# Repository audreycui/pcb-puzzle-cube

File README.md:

# pcb-puzzle-cube
Mechanical, Optical, &amp; Electronic Puzzle Cube

I made a puzzle cube for my wonderful electronics lab instructor who is also a professional trumpet player! A lot of the fun in making this was designing my circuits and mechanical components around 5 milled PCBs soldered together into a cube. Puzzles involve "playing" a sequence of notes on a flex PCB capacitive trumpet and using a butterfly flexure to align a laser path through a beamsplitter.

## Milled PCBs
From left to right, the sides of the cube include: 
1. WS2812b LEDs 
2. resistor combinations with pads for probing
3. laser diode regulated by a LM317 circuit and switched on/off electronically with a 2N7002 MOSFET 
4. QTPy ESP32 microcontroller
   
Sides 1 & 4 also include a photoresistor to detect laser beam alignment.

And the bottom:

5. 5V power jack, switches for the board power and laser power, mount for butterfly flexure

## Trumpet Capacitive Touch FlexPCB
I really wanted an excuse to fab a flexPCB, so I did so here. FlexPCB files are located in the <code>trumpet</code> subfolder. 

The connector end of the trumpet was designed to fit in a 6pin/1mm FPC connector. I ended up just soldering it directly to the board though, since I ended up finding an end mill small enough to carve out the 1mm pitch pads. It also helped me avoid buying an extra component. 

## Video Demo
Watch a video demo of the cube being solved [here](https://www.youtube.com/watch?v=AHTcb9tr4TA) :D

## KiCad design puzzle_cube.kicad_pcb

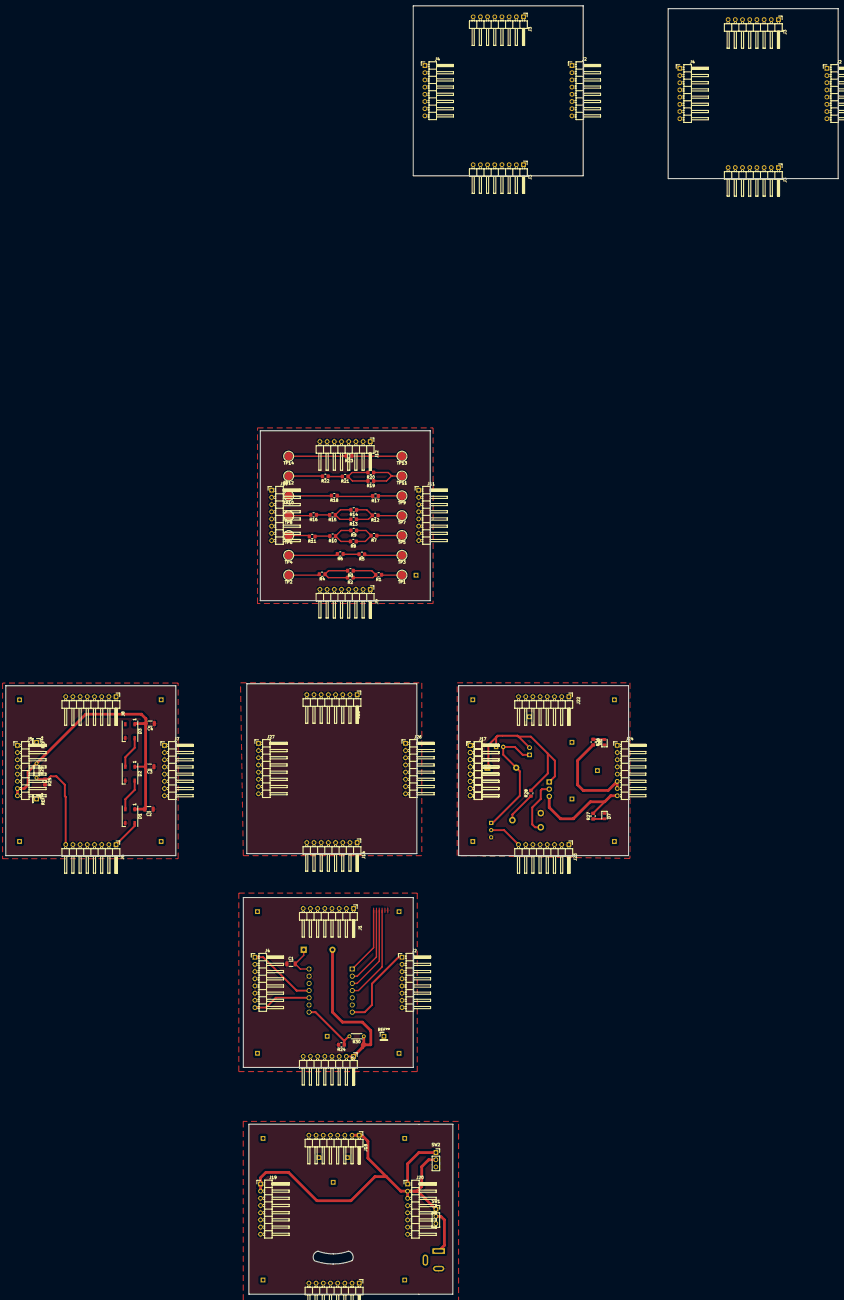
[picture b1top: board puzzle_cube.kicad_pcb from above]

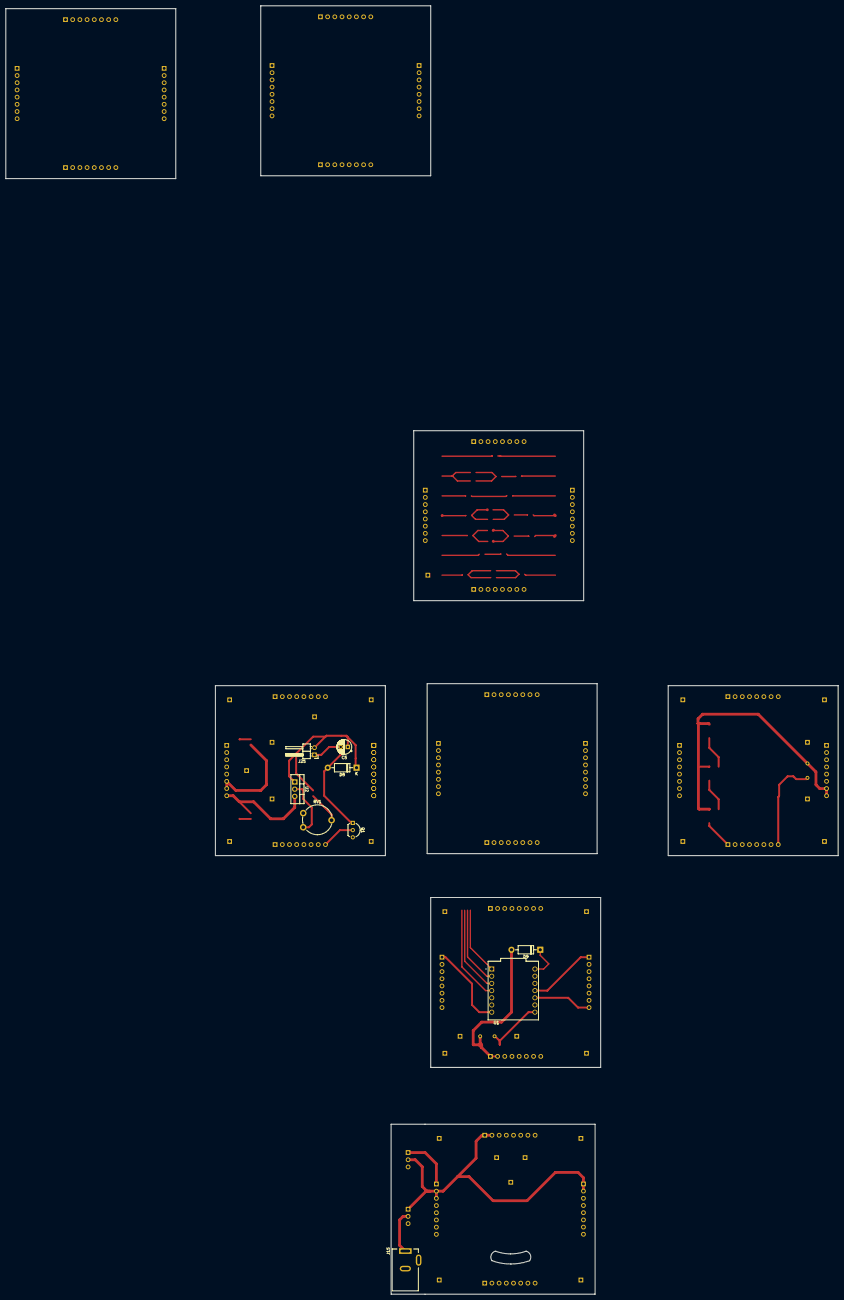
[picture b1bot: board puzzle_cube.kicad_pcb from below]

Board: 2 copper layers, 293.8 x 454.8 mm, 98 parts (9 on the bottom side), 47 nets.

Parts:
C1: C; C_1206_3216Metric
C2, C3, C4: 100uF; C_1206_3216Metric
C5: C; CP_Radial_D5.0mm_P2.50mm
D1, D2, D3: WS2812B; LED_WS2812B_PLCC4_5.0x5.0mm_P3.2mm
D6, D7: LED; LED_0805_2012Metric
D8, D9: 1N4007; D_DO-41_SOD81_P10.16mm_Horizontal
J1: qtpy2capacitive; PinHeader_1x08_P2.54mm_Horizontal
J2, J2#2, J3, J3#2, J3#4, J3#5, J4, J4#3: Conn_01x08_Pin; PinHeader_1x08_P2.54mm_Horizontal
J2#3: qtpy2laser; PinHeader_1x08_P2.54mm_Horizontal
J3#3: qtpy2beamsplitter; PinHeader_1x08_P2.54mm_Horizontal
J4#2: qtpy2leds; PinHeader_1x08_P2.54mm_Horizontal
J5: leds2beamsplitter; PinHeader_1x08_P2.54mm_Horizontal
J6: leds2qtpy; PinHeader_1x08_P2.54mm_Horizontal
J7: leds2capacitive; PinHeader_1x08_P2.54mm_Horizontal
J8: leds2resistors; PinHeader_1x08_P2.54mm_Horizontal
J9: resistors2capacitive; PinHeader_1x08_P2.54mm_Horizontal
J10: resistors2leds; PinHeader_1x08_P2.54mm_Horizontal
J11: resistors2laser; PinHeader_1x08_P2.54mm_Horizontal
J12: resistors2beamsplitter; PinHeader_1x08_P2.54mm_Horizontal
J13: trumpet_flexcable; 6pin_1.00pitch_FPC
J14: capacitive2qtpy; PinHeader_1x08_P2.54mm_Horizontal
J15: Barrel_Jack_MountingPin; BarrelJack_Kycon_KLDX-0202-xC_Horizontal
J17, J17#2: beamsplitter2resistors; PinHeader_1x08_P2.54mm_Horizontal
J18: beamsplitter2qtpy; PinHeader_1x08_P2.54mm_Horizontal
J19: beamsplitter2leds; PinHeader_1x08_P2.54mm_Horizontal
J20: beamsplitter2laser; PinHeader_1x08_P2.54mm_Horizontal
J21: laser2capacitve; PinHeader_1x08_P2.54mm_Horizontal
J22: laser2resistors; PinHeader_1x08_P2.54mm_Horizontal
J23: laser2qtpy; PinHeader_1x08_P2.54mm_Horizontal
J24: laser2beamsplitter; PinHeader_1x08_P2.54mm_Horizontal
J25: laser connector; PinHeader_1x02_P2.54mm_Horizontal
J26: capacitive2laser; PinHeader_1x08_P2.54mm_Horizontal
J27: capacitive2led; PinHeader_1x08_P2.54mm_Horizontal
J28: capacitive2resistor; PinHeader_1x08_P2.54mm_Horizontal
Q1: NPN; TO-92L_Inline_Wide
R1: 200; R_0805_2012Metric_Pad1.20x1.40mm_HandSolder
R2, R3: 120; R_0805_2012Metric_Pad1.20x1.40mm_HandSolder
R4: 62; R_0805_2012Metric_Pad1.20x1.40mm_HandSolder
R5, R7, R12, R17: 430; R_0805_2012Metric_Pad1.20x1.40mm_HandSolder
R6, R10, R15, R18: 10; R_0805_2012Metric_Pad1.20x1.40mm_HandSolder
R8, R9, R13, R14: 68; R_0805_2012Metric_Pad1.20x1.40mm_HandSolder
R11, R16: 20; R_0805_2012Metric_Pad1.20x1.40mm_HandSolder
R19, R20: 680; R_0805_2012Metric_Pad1.20x1.40mm_HandSolder
R21: 51; R_0805_2012Metric_Pad1.20x1.40mm_HandSolder
R22: 1; R_0805_2012Metric_Pad1.20x1.40mm_HandSolder
R23: 330; R_0805_2012Metric_Pad1.20x1.40mm_HandSolder
R24, R25: 10k; R_0805_2012Metric_Pad1.20x1.40mm_HandSolder
R26, R27: 1k; R_0805_2012Metric_Pad1.20x1.40mm_HandSolder
R28: R_US; R_0805_2012Metric_Pad1.20x1.40mm_HandSolder
R29, R30: R_Photo; R_Axial_DIN0204_L3.6mm_D1.6mm_P5.08mm_Horizontal
RV1: R_Potentiometer_Trim_US; Potentiometer_Piher_PT-10-V10_Vertical
SW1: power; PinSocket_1x03_P2.54mm_Vertical
SW2: laser; PinSocket_1x03_P2.54mm_Vertical
TP1, TP2, TP3, TP4, TP5, TP6, TP7, TP8, TP9, TP10, TP11, TP12, TP13, TP14: TestPoint; TestPoint_Pad_D3.0mm
U1: ADAFRUIT_QT_PY; MODULE_ADAFRUIT_QT_PY
U2: LM317L_TO92; TO-220-3_Vertical

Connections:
+5V: C2.2, C3.2, C4.2, D1.1 (VDD), D2.1 (VDD), D3.1 (VDD), D9.2 (A), J3#3.1, J3#3.2, J5.7, J5.8, J18.1, J18.2, J19.1, J19.2, J20.2, J20.3, J24.6, J24.7, R26.2, R29.1, R30.1, SW1.1 (A), SW2.2 (B)
/beamsplitter/5V_beforeswitch: J15.1, SW1.2 (B)
/beamsplitter/laser_power: J20.1, J24.8, R27.2, SW2.1 (A), U2.3 (VI)
/laser/laser_base: J2#3.1, J23.8, Q1.2 (B), U1.7 (A6/D6/TX)
/leds_detector/D1: D1.2 (DOUT), D2.4 (DIN)
/leds_detector/D2: D2.2 (DOUT), D3.4 (DIN)
/leds_detector/detector_2: J4#2.8, J6.8, R25.1, R29.2, U1.10 (A9/D9/MISO)
/leds_detector/leds: D1.4 (DIN), J4#2.1, J6.1, U1.11 (A10/D10/MOSI)
/qtpy/detector_1: R24.1, R30.2, U1.8 (A7/D7/RX)
/qtpy/enter: J13.1, U1.1 (A0/D0/DAC)
/qtpy/trumpet_1: J13.2, U1.2 (A1/D1)
/qtpy/trumpet_2: J13.3, U1.3 (A2/D2)
/qtpy/trumpet_3: J13.4, U1.4 (A3/D3)
GND: C1.1, C2.1, C3.1, C4.1, D1.3 (VSS), D2.3 (VSS), D3.3 (VSS), D6.1 (K), D7.1 (K), J1.1, J1.2, J1.3, J1.4, J1.5, J1.6, J1.7, J1.8, J2#3.2, J2#3.3, J2#3.4, J2#3.5, J2#3.6, J2#3.7, J2#3.8, J3#3.3, J3#3.4, J3#3.5, J3#3.6, J3#3.7, J3#3.8, J4#2.2, J4#2.3, J4#2.4, J4#2.5, J4#2.6, J4#2.7, J5.1, J5.2, J5.3, J5.4, J5.5, J5.6, J6.2, J6.3, J6.4, J6.5, J6.6, J6.7, J7.1, J7.2, J7.3, J7.4, J7.5, J7.6, J7.7, J7.8, J8.1, J8.2, J8.3, J8.4, J8.5, J8.6, J8.7, J8.8, J9.1, J9.2, J9.3, J9.4, J9.5, J9.6, J9.7, J9.8, J10.1, J10.2, J10.3, J10.4, J10.5, J10.6, J10.7, J10.8, J11.1, J11.2, J11.3, J11.4, J11.5, J11.6, J11.7, J11.8, J12.1, J12.2, J12.3, J12.4, J12.5, J12.6, J12.7, J12.8, J13.5, J13.6, J14.1, J14.2, J14.3, J14.4, J14.5, J14.6, J14.7, J14.8, J15.2, J17.1, J17.2, J17.3, J17.4, J17.5, J17.6, J17.7, J17.8, J17#2.1, J17#2.2, J17#2.3, J17#2.4, J17#2.5, J17#2.6, J17#2.7, J17#2.8, J18.3, J18.4, J18.5, J18.6, J18.7, J18.8, J19.3, J19.4, J19.5, J19.6, J19.7, J19.8, J20.4, J20.5, J20.6, J20.7, J20.8, J21.1, J21.2, J21.3, J21.4, J21.5, J21.6, J21.7, J21.8, J22.1, J22.2, J22.3, J22.4, J22.5, J22.6, J22.7, J22.8, J23.1, J23.2, J23.3, J23.4, J23.5, J23.6, J23.7, J24.1, J24.2, J24.3, J24.4, J24.5, J26.1, J26.2, J26.3, J26.4, J26.5, J26.6, J26.7, J26.8, J27.1, J27.2, J27.3, J27.4, J27.5, J27.6, J27.7, J27.8, J28.1, J28.2, J28.3, J28.4, J28.5, J28.6, J28.7, J28.8, Q1.3 (E), R24.2, R25.2, RV1.3, U1.13 (GND)
unnamed: D6.2 (A), R26.1
unnamed: D7.2 (A), R27.1
unnamed: C5.2, D8.2 (A), J25.1, Q1.1 (C)
unnamed: C5.1, D8.1 (K), J25.2, R28.2, U2.1 (ADJ)
unnamed: C1.2, D9.1 (K), U1.14 (5V)
unnamed: R1.1, TP1.1
unnamed: R1.2, R2.1, R3.1
unnamed: R2.2, R3.2, R4.1
unnamed: R4.2, TP2.1
unnamed: R5.1, TP3.1
unnamed: R5.2, R6.1
unnamed: R6.2, TP4.1
unnamed: R7.1, TP5.1
unnamed: R7.2, R8.1, R9.1
unnamed: R8.2, R9.2, R10.1
unnamed: R10.2, R11.1
unnamed: R11.2, TP6.1
unnamed: R12.1, TP7.1
unnamed: R12.2, R13.1, R14.1
unnamed: R13.2, R14.2, R15.1
unnamed: R15.2, R16.1
unnamed: R16.2, TP8.1
unnamed: R17.1, TP9.1
unnamed: R17.2, R18.1
unnamed: R18.2, TP10.1
unnamed: R19.1, R20.1, TP11.1
unnamed: R19.2, R20.2, R21.1
unnamed: R21.2, R22.1
unnamed: R22.2, TP12.1
unnamed: R23.1, TP13.1
unnamed: R23.2, TP14.1
unnamed: R28.1, RV1.2
unnamed: RV1.1, U2.2 (VO)

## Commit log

2024-09-20 init commit
